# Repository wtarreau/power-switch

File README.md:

power-switch
============

This project consists in controlling multiple power outputs for various
devices. Some USB-PD multi-port controllers only require minor modifications
to support being controlled and deliver power to individual devices.

The PCA9554D based board under boards/pca9554d-v3 controls 8 individual
USB-PD channels over I2C.

Possible variations
===================

The project requires and open-drain output to control the CC1 line of
the USB-PD boards. Other devices such as 74HC596 or TPIC6B595 offer
open-drain variants of the ubiquitous 74HC595 that only requires 3
signals to control 8 lines (clock, data, register clock), and can
trivially be daisy-chained.

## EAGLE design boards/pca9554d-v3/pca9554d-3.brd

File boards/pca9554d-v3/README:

2024-10-06 - v3

This is the 3rd version of the board using a PCA9554D (same pinout as
PCF8574D which should also work).

- open drain outputs using MOSFETs and 200 ohm resistors to protect
  against short-circuits

- GND placed left of output 0 instead of right of output 7

Files in this directory:
- bottom-copper = copper traces for components side (60 microns per pixel)
- bottom-cream = solder mask for components side (60 microns per pixel)
- pca9554d-3.sch = schematic (eagle 7.7 format)
- pca9554d-3.brd = board (eagle 7.7 format)
- schematic.png = rendered schematic

Board files were rendered at 60 microns per pixel (423.33 DPI) for laser
engraving or CNC etching but may also be printed for UV etching.

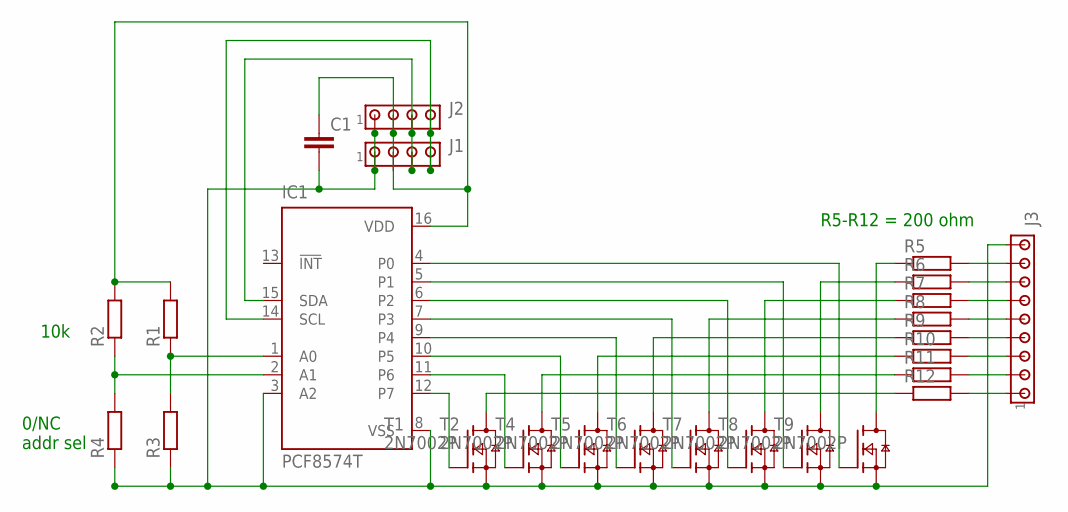
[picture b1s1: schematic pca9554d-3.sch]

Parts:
C1: C-EUC1206; C1206
IC1: PCF8574T; SO16W
J1, J2: MTA04-100; 10X04MTA
J3: MTA09-100; 10X09MTA
R1, R2: R-EU_R0805; R0805
R3, R4: R-EU_R0402; R0402
R5, R6, R7, R8, R9, R10, R11, R12: R-EU_R0805W; R0805W
T1, T2, T4, T5, T6, T7, T8, T9: 2N7002P; SOT23

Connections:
unnamed: C1.1, IC1.16 (VDD), J1.2, J2.2, R1.2, R2.2
unnamed: J3.8, R5.2
unnamed: IC1.15 (SDA), J1.3, J2.3
unnamed: IC1.14 (SCL), J1.4, J2.4
unnamed: IC1.1 (A0), R1.1, R3.2
unnamed: IC1.2 (A1), R2.1, R4.2
unnamed: IC1.12 (P7), T1.1 (G)
unnamed: J3.7, R6.2
unnamed: J3.6, R7.2
unnamed: J3.5, R8.2
unnamed: J3.4, R9.2
unnamed: J3.3, R10.2
unnamed: J3.2, R11.2
unnamed: J3.1, R12.2
unnamed: IC1.11 (P6), T2.1 (G)
unnamed: C1.2, IC1.3 (A2), IC1.8 (VSS), J1.1, J2.1, J3.9, R3.1, R4.1, T1.2 (S), T2.2 (S), T4.2 (S), T5.2 (S), T6.2 (S), T7.2 (S), T8.2 (S), T9.2 (S)
unnamed: IC1.10 (P5), T4.1 (G)
unnamed: IC1.9 (P4), T5.1 (G)
unnamed: IC1.7 (P3), T6.1 (G)
unnamed: IC1.6 (P2), T7.1 (G)
unnamed: IC1.5 (P1), T8.1 (G)
unnamed: IC1.4 (P0), T9.1 (G)
unnamed: R5.1, T9.3 (D)
unnamed: R6.1, T8.3 (D)
unnamed: R7.1, T7.3 (D)
unnamed: R8.1, T6.3 (D)
unnamed: R9.1, T5.3 (D)
unnamed: R10.1, T4.3 (D)
unnamed: R11.1, T2.3 (D)
unnamed: R12.1, T1.3 (D)

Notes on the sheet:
R5-R12 = 200 ohm
0/NC addr sel
10k

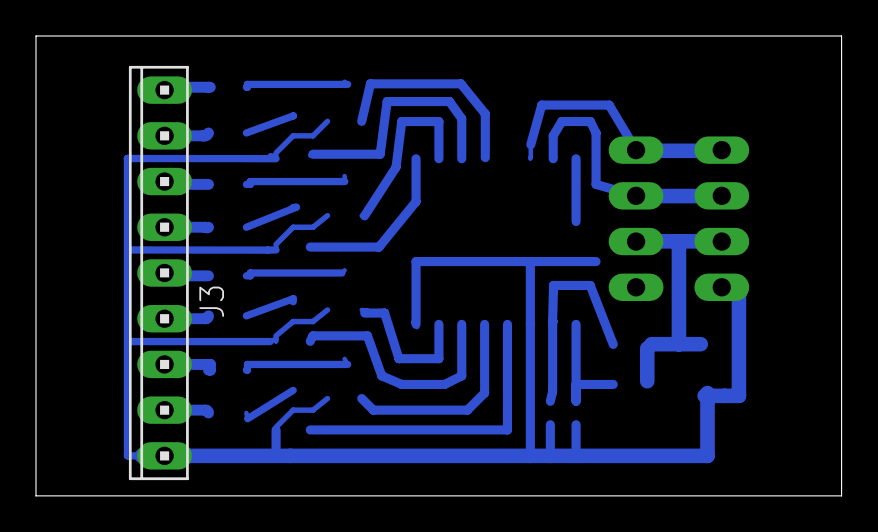
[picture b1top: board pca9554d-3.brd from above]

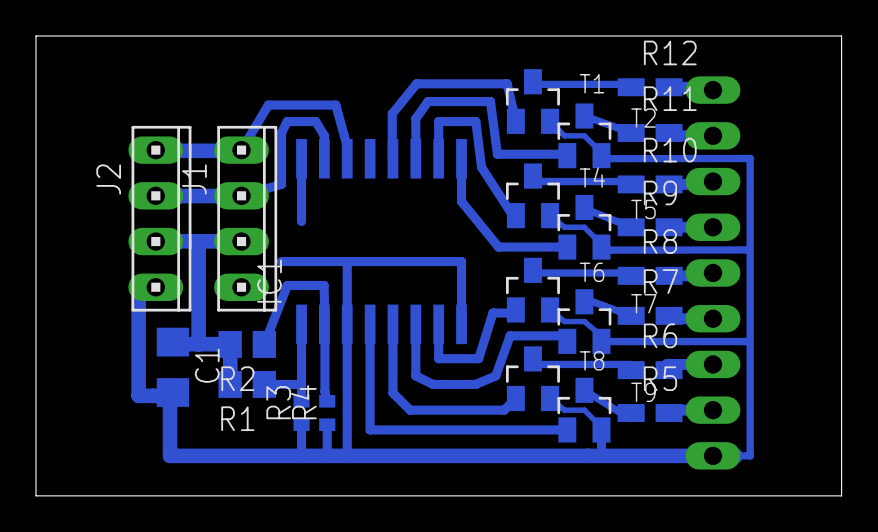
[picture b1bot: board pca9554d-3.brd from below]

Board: 2 copper layers, 44.8 x 25.5 mm, 25 parts (24 on the bottom side), 30 nets.

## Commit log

2024-10-06 Add pca9554d board (schematic, board, renderings and photos)
    This contains photos of both v2 and v3 board, though the schematic,
    renderings etc are only for v3.
2024-10-06 Add README.md
    Also mention possible GPIO-based variations (74HC595, 74HC596 etc).
2024-10-06 Add scripts and sample config
    The psw script relies on psw.conf to find port numbers and GPIOs. The
    names are indicative and used only for listing.
